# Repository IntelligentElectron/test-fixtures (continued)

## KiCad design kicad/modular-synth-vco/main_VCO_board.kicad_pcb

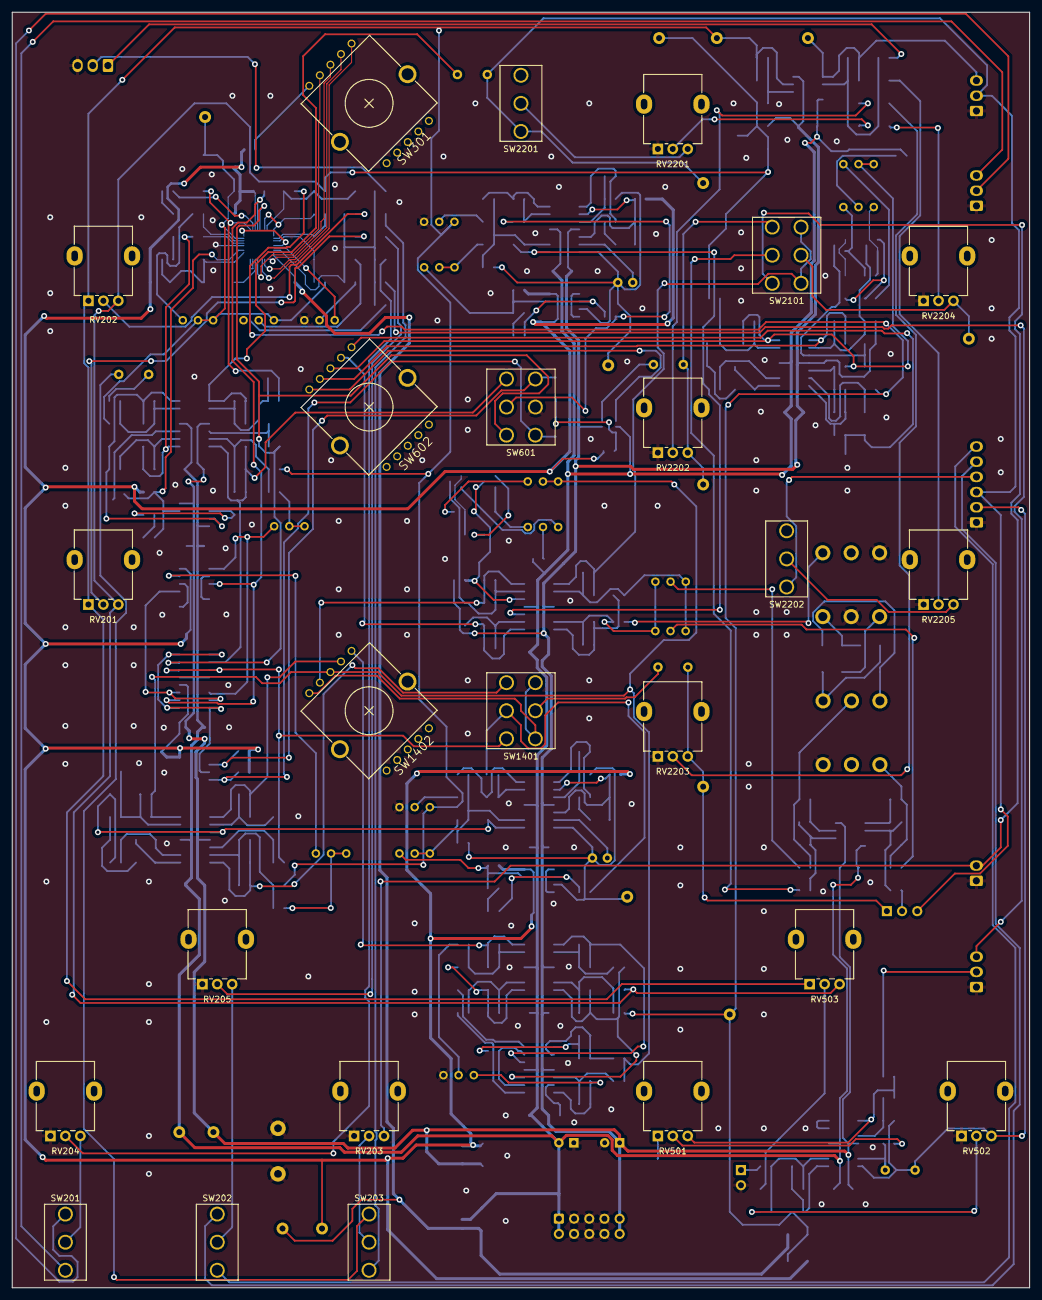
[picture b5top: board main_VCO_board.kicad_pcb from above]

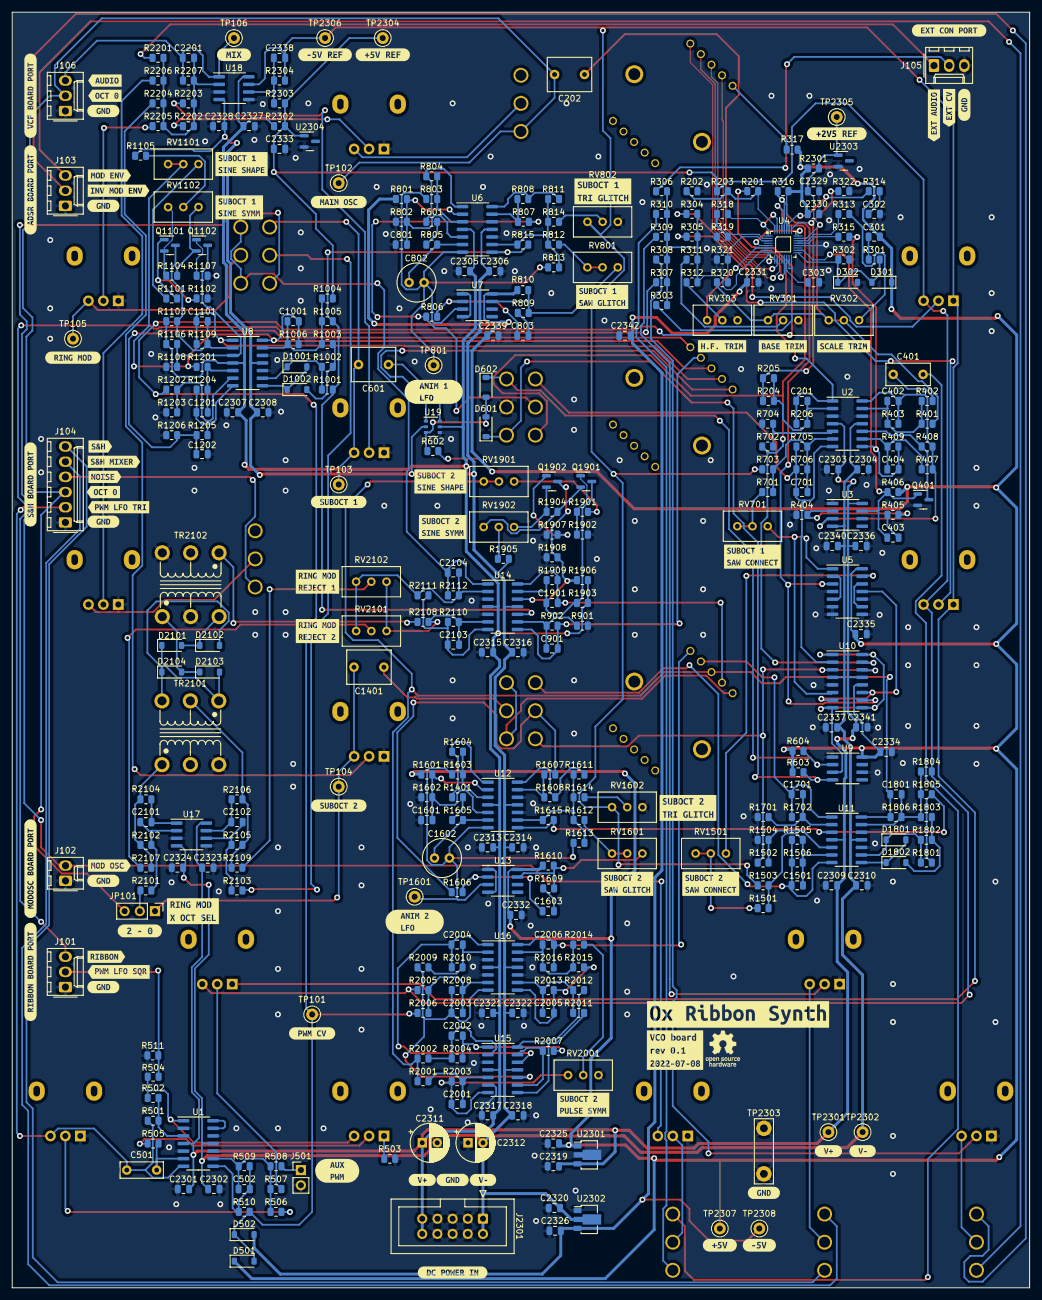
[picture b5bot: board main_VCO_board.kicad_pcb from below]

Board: 2 copper layers, 170.2 x 213.4 mm, 432 parts (408 on the bottom side), 215 nets.

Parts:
C201, C402, C403, C404, C502, C803, C901, C1001, C1603, C1701, C1801, C2003, C2004, C2005, C2006, C2101, C2102, C2103, C2104: 100p; C_0805_2012Metric
C202, C601, C1401: 1u; C_Rect_L7.2mm_W5.5mm_P5.00mm_FKS2_FKP2_MKS2_MKP2
C301, C801, C1601: 10u; C_0805_2012Metric
C302, C1101, C1202, C1901: 10n; C_0805_2012Metric
C303: 3N9 COG; C_0805_2012Metric
C401: 10u BP; C_Rect_L7.2mm_W3.5mm_P5.00mm_FKS2_FKP2_MKS2_MKP2
C501: 220n; C_Rect_L7.0mm_W2.5mm_P5.00mm
C701, C1201, C1501, C2001, C2002, C2201: 10p; C_0805_2012Metric
C802, C1602: 10u BP; C_Radial_D6.3mm_H5.0mm_P2.50mm
C2301, C2302, C2303, C2304, C2305, C2306, C2307, C2308, C2309, C2310, C2313, C2314, C2315, C2316, C2317, C2318, C2321, C2322, C2323, C2324, C2325, C2326, C2327, C2328, C2329, C2330, C2331, C2332, C2333, C2334, C2335, C2336, C2337, C2338, C2339, C2340, C2341, C2342: 100n; C_0805_2012Metric
C2311, C2312: 10u; CP_Radial_D6.3mm_P2.50mm
C2319, C2320: 470n; C_0805_2012Metric
D301, D302, D601, D602, D1001, D1002, D1801, D1802: 1N4148W; D_SOD-123
D501, D502, D2101, D2102, D2103, D2104: BAT48ZFILM; D_SOD-123
J101: ribbon_port; Molex_KK-254_AE-6410-03A_1x03_P2.54mm_Vertical
J102: modosc_port; Molex_KK-254_AE-6410-02A_1x02_P2.54mm_Vertical
J103: ADSR_port; Molex_KK-254_AE-6410-03A_1x03_P2.54mm_Vertical
J104: S&H_port; Molex_KK-254_AE-6410-06A_1x06_P2.54mm_Vertical
J105: ext_con; Molex_KK-254_AE-6410-03A_1x03_P2.54mm_Vertical
J106: vcf_port; Molex_KK-254_AE-6410-03A_1x03_P2.54mm_Vertical
J501: aux_pwm; PinHeader_1x02_P2.54mm_Vertical
J2301: power_entry; IDC-Header_2x05_P2.54mm_Vertical
JP101: rm_x_select; PinHeader_1x03_P2.54mm_Vertical
Q401: 2N7002; SOT-23
Q1101, Q1102, Q1901, Q1902: MMBT3904; SOT-23
R201: 150k; R_0805_2012Metric
R202: 56k; R_0805_2012Metric
R203, R804, R1004, R1006, R1604, R1804, R1806: 120k; R_0805_2012Metric
R204, R205, R304, R306, R307, R308, R309, R310, R311, R317, R401, R403, R405, R501, R505, R506, R507, R508, R509, R602, R704, R705, R706, R805, R807, R808, R809, R811, R813, R815, R902, R1203, R1504, R1505, R1506, R1605, R1607, R1608, R1609, R1611, R1613, R1615, R1702, R2002, R2004, R2008, R2009, R2010, R2011, R2012, R2015, R2101, R2102, R2103, R2105, R2107, R2108, R2109, R2110, R2111, R2201, R2202, R2203, R2204, R2205: 100k; R_0805_2012Metric
R206, R702, R703, R814, R1502, R1503, R1614, R2005, R2006: 200k; R_0805_2012Metric
R301, R302, R406, R603, R604, R803, R1103, R1106, R1201, R1603, R1903, R1906, R2001, R2303, R2304: 10k; R_0805_2012Metric
R303, R402, R901, R1701, R2206: 33k; R_0805_2012Metric
R305: 1M; R_0805_2012Metric
R312, R502: 270k; R_0805_2012Metric
R313: 47k; R_0805_2012Metric
R314: 270; R_0805_2012Metric
R315: 470k; R_0805_2012Metric
R316, R319, R321, R2302: 4k7; R_0805_2012Metric
R318: 3k9; R_0805_2012Metric
R320, R1108, R1109, R1908, R1909: 12k; R_0805_2012Metric
R322, R1105, R1905: 18k; R_0805_2012Metric
R404, R503: 100; R_0805_2012Metric
R407, R408, R409, R2013: 20k; R_0805_2012Metric
R504, R1102, R1107, R1205, R1902, R1907, R2007: 2k2; R_0805_2012Metric
R510, R511, R806, R810, R1206, R1606, R1610: 1k; R_0805_2012Metric
R601: 1M5; R_0805_2012Metric
R701, R812, R1501, R1612, R2016: 180k; R_0805_2012Metric
R801, R1601: 8k2; R_0805_2012Metric
R802, R1602: 2k7; R_0805_2012Metric
R1001, R1002, R1005, R1202, R1801, R1802, R1805: 15k; R_0805_2012Metric
R1003, R1803: 7k5; R_0805_2012Metric
R1101, R1901: 27k; R_0805_2012Metric
R1104, R1904: 390; R_0805_2012Metric
R1204, R2003: 10M; R_0805_2012Metric
R1401: 2M2; R_0805_2012Metric
R2014: 220k; R_0805_2012Metric
R2104, R2106: 330; R_0805_2012Metric
R2112: 560k; R_0805_2012Metric
R2207: 82k; R_0805_2012Metric
R2301: 1k8; R_0805_2012Metric
RV201, RV202: 10k; Potentiometer_Alpha_RD901F-40-00D_Single_Vertical
RV203, RV204, RV205, RV501, RV502, RV503, RV2201, RV2202, RV2203, RV2204, RV2205: 100k; Potentiometer_Alpha_RD901F-40-00D_Single_Vertical
RV301, RV302, RV303, RV802, RV1602: 5k; Potentiometer_Bourns_3296W_Vertical
RV701, RV801, RV1101, RV1102, RV1501, RV1601, RV1901, RV1902, RV2001, RV2101, RV2102: 50k; Potentiometer_Bourns_3296W_Vertical
SW201, SW202, SW203: SW_SPDT_CO; SPDT_mini_toggle
SW301, SW602, SW1402: SR1712F-0204; SR1712F_rotary_switch
SW601, SW1401, SW2101: SW_DPDT_CO; DPDT_mini_toggle
SW2201, SW2202: SW_SPDT; SPDT_mini_toggle
TP101: pwm_cv; TestPoint_Keystone_5000-5004_Miniature
TP102: oct_0; TestPoint_Keystone_5000-5004_Miniature
TP103: oct_1; TestPoint_Keystone_5000-5004_Miniature
TP104: oct_2; TestPoint_Keystone_5000-5004_Miniature
TP105: ring_mod; TestPoint_Keystone_5000-5004_Miniature
TP106: mix; TestPoint_Keystone_5000-5004_Miniature
TP801, TP1601: anim_LFO; TestPoint_Keystone_5000-5004_Miniature
TP2301: V+; TestPoint_Keystone_5000-5004_Miniature
TP2302: V-; TestPoint_Keystone_5000-5004_Miniature
TP2303: GND; TestPoint_Bridge_Pitch7.62mm_Drill1.3mm
TP2304: +5_REF; TestPoint_Keystone_5000-5004_Miniature
TP2305: +2V5; TestPoint_Keystone_5000-5004_Miniature
TP2306: -5_REF; TestPoint_Keystone_5000-5004_Miniature
TP2307: +5; TestPoint_Keystone_5000-5004_Miniature
TP2308: -5; TestPoint_Keystone_5000-5004_Miniature
TR2101, TR2102: Triad_TY_141P; Triad_TY-141P
U1, U2, U6, U8, U11, U12, U14, U15, U16: TL074; SOIC-14_3.9x8.7mm_P1.27mm
U3, U7, U13: LM311; SOIC-8_3.9x4.9mm_P1.27mm
U4: SSI2130; PQN32_HandSoldering
U5: 4013; SOIC-14_3.9x8.7mm_P1.27mm
U9: LM555xM; SOIC-8_3.9x4.9mm_P1.27mm
U10: DG413xY; SOIC-16_3.9x9.9mm_P1.27mm
U17: NE5532; SOIC-8_3.9x4.9mm_P1.27mm
U18: TL072; SOIC-8_3.9x4.9mm_P1.27mm
U19: DG447DV; TSOP-6_1.65x3.05mm_P0.95mm
U2301: L78L05_SOT89; SOT-89-3
U2302: L79L05_SOT89; SOT-89-3
U2303: LM4040C-2.5; SOT-23
U2304: LM4040DBZ-5; SOT-23
kibuzzard-62AC7A9F: G***; kibuzzard-62AC7A9F
kibuzzard-62AF4ADF, kibuzzard-62AF4ADF#2, kibuzzard-62AF4ADF#3, kibuzzard-62AF4ADF#4, kibuzzard-62AF4ADF#5, kibuzzard-62AF4ADF#6, kibuzzard-62AF4ADF#7, kibuzzard-62AF4ADF#8: G***; kibuzzard-62AF4ADF
kibuzzard-62AF4B86: G***; kibuzzard-62AF4B86
kibuzzard-62AF4B95: G***; kibuzzard-62AF4B95
kibuzzard-62AF4BB4: G***; kibuzzard-62AF4BB4
kibuzzard-62AF4BC9: G***; kibuzzard-62AF4BC9
kibuzzard-62AF4BDF: G***; kibuzzard-62AF4BDF
kibuzzard-62AF4C29: G***; kibuzzard-62AF4C29
kibuzzard-62AF4C42: G***; kibuzzard-62AF4C42
kibuzzard-62AF4C77: G***; kibuzzard-62AF4C77
kibuzzard-62AF4C86, kibuzzard-62AF4C86#2: G***; kibuzzard-62AF4C86
kibuzzard-62AF4CA7: G***; kibuzzard-62AF4CA7
kibuzzard-62AF4CDD: G***; kibuzzard-62AF4CDD
kibuzzard-62AF4D2D: G***; kibuzzard-62AF4D2D
kibuzzard-62AF4D5F: G***; kibuzzard-62AF4D5F
kibuzzard-62AF4D40: G***; kibuzzard-62AF4D40
kibuzzard-62AF4D77: G***; kibuzzard-62AF4D77
kibuzzard-62AF4D92: G***; kibuzzard-62AF4D92
kibuzzard-62AF7B29: G***; kibuzzard-62AF7B29
kibuzzard-62AF7B45: G***; kibuzzard-62AF7B45
kibuzzard-62AF7B57: G***; kibuzzard-62AF7B57
kibuzzard-62AF7BF6: G***; kibuzzard-62AF7BF6
kibuzzard-62AF7C0F: G***; kibuzzard-62AF7C0F
kibuzzard-62AF7C6F: G***; kibuzzard-62AF7C6F
kibuzzard-62AF7C97: G***; kibuzzard-62AF7C97
kibuzzard-62AF7CA9: G***; kibuzzard-62AF7CA9
kibuzzard-62AF7CE8: G***; kibuzzard-62AF7CE8
kibuzzard-62AF7D4C: G***; kibuzzard-62AF7D4C
kibuzzard-62AF7D08: G***; kibuzzard-62AF7D08
kibuzzard-62AF7D9E: G***; kibuzzard-62AF7D9E
kibuzzard-62AF7D77: G***; kibuzzard-62AF7D77
kibuzzard-62AF7D91: G***; kibuzzard-62AF7D91
kibuzzard-62AF794D: G***; kibuzzard-62AF794D
kibuzzard-62AF7971, kibuzzard-62AF7971#2: G***; kibuzzard-62AF7971
kibuzzard-62AF7983, kibuzzard-62AF7983#2: G***; kibuzzard-62AF7983
kibuzzard-62B06A0C: G***; kibuzzard-62B06A0C
kibuzzard-62B8B2A5: G***; kibuzzard-62B8B2A5
kibuzzard-62B8B20F: G***; kibuzzard-62B8B20F
kibuzzard-62B8B280: G***; kibuzzard-62B8B280
kibuzzard-62B057A7: G***; kibuzzard-62B057A7
kibuzzard-62B062C4: G***; kibuzzard-62B062C4
kibuzzard-62B0579A: G***; kibuzzard-62B0579A
kibuzzard-62B0634B: G***; kibuzzard-62B0634B
kibuzzard-62B05771: G***; kibuzzard-62B05771
kibuzzard-62B05783: G***; kibuzzard-62B05783
kibuzzard-62B05837: G***; kibuzzard-62B05837
kibuzzard-62C86AB4: G***; kibuzzard-62C86AB4
kibuzzard-62C860A0: G***; kibuzzard-62C860A0
kibuzzard-62C861D2: G***; kibuzzard-62C861D2
kibuzzard-62C861DC: G***; kibuzzard-62C861DC
kibuzzard-62C862AA: G***; kibuzzard-62C862AA
kibuzzard-62C863A9: G***; kibuzzard-62C863A9
kibuzzard-62C863C2: G***; kibuzzard-62C863C2
kibuzzard-62C8621C: G***; kibuzzard-62C8621C
kibuzzard-62C8628B: G***; kibuzzard-62C8628B
kibuzzard-62C86136: G***; kibuzzard-62C86136
kibuzzard-62C86170: G***; kibuzzard-62C86170

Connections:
+2V5_REF: C2329.1, R303.2, R320.2, R401.2, R2301.2, RV301.3, RV302.2, RV302.3, TP2305.1, U4.23 (vref), U2303.1 (K)
+5V: C301.2, C2325.1, C2330.1, C2332.1, C2334.1, C2335.1, C2339.1, D301.1 (K), D501.1 (K), R316.2, R317.1, R406.2, R602.2, R603.1, R604.1, R801.1, R810.2, R1601.1, R1610.2, R2301.1, TP2307.1, U4.27 (V+), U5.14 (VDD), U7.8 (V+), U9.8 (VCC), U10.12 (VL), U13.8 (V+), U2301.1 (OUT)
+5V_REF: C2333.1, R203.1, R1004.2, R1804.2, R2005.1, R2302.2, R2303.2, RV201.3, RV202.3, RV503.3, TP2304.1, U2304.1 (K)
+15V: C2301.1, C2303.1, C2305.1, C2307.1, C2309.1, C2311.1, C2313.1, C2315.1, C2317.1, C2319.1, C2321.1, C2323.1, C2327.1, C2336.1, C2341.1, J2301.9, J2301.10, R1103.1, R1106.1, R1903.1, R1906.1, R2302.1, TP2301.1, U1.4 (V+), U2.4 (V+), U3.8 (V+), U6.4 (V+), U8.4 (V+), U10.13 (V+), U11.4 (V+), U12.4 (V+), U14.4 (V+), U15.4 (V+), U16.4 (V+), U17.8 (V+), U18.8 (V+), U19.5 (V+), U2301.3 (IN)
-5V: C2326.2, C2331.2, C2342.2, D502.2 (A), TP2308.1, U4.8 (V-), U2302.3 (VO)
-5V_REF: C2338.1, R703.1, R1503.1, R2304.1, RV201.1, RV202.1, RV503.1, RV802.3, RV1602.3, TP2306.1, U18.7
-15V: C2302.2, C2304.2, C2306.2, C2308.2, C2310.2, C2312.2, C2314.2, C2316.2, C2318.2, C2320.2, C2322.2, C2324.2, C2328.2, C2337.2, C2340.2, J2301.1, J2301.2, R1105.2, R1905.2, TP2302.1, U1.11 (V-), U2.11 (V-), U3.4 (V-), U6.11 (V-), U8.11 (V-), U10.4 (V-), U11.11 (V-), U12.11 (V-), U14.11 (V-), U15.11 (V-), U16.11 (V-), U17.4 (V-), U18.4 (V-), U19.2 (V-), U2302.2 (VI)
/EXT_AUDIO: J105.1, R2201.1
/MOD_OSC: J102.2, RV203.3, SW2101.1
/NOISE: J104.4, SW2202.1 (A)
/OCTAVE_0: C202.2, J104.3, J106.2, JP101.3 (B), SW2201.1 (A), TP102.1
/OCTAVE_1: C601.2, RV2202.3, SW2101.3, TP103.1
/OCTAVE_2: C1401.2, JP101.1 (A), RV2203.3, TP104.1
/PWM_LFO_SQR: J101.2, R504.1, R511.2
/PWM_LFO_TRI: C501.2, J104.2, R501.2, RV502.3, U1.7
/PWM_generator/PWM_CV_OUT: D501.2 (A), D502.1 (K), R201.1, R510.2, R1202.1, R2006.1, TP101.1
/audio_mixer/OUT: C2201.2, J106.3, R2207.2, TP106.1, U18.1
/audio_mixer/RING_MOD: RV2204.3, SW2101.5, TP105.1
/main_VCO/EXT_CV: J105.2, R306.2
/main_VCO/MOD_ENV_DOWN: J103.2, SW201.3
/main_VCO/MOD_ENV_UP: J103.3, SW201.1
/main_VCO/RIBBON_CV: J101.3, R307.2
/main_VCO/S_AND_H: J104.6, SW202.1
/main_VCO/S_AND_H_MIXER: J104.5, SW202.3
/main_VCO/VCO_core/COARSE_TUNE_IN: R304.2, RV202.2
/main_VCO/VCO_core/FINE_TUNE_IN: R305.2, RV201.2
/main_VCO/VCO_core/LIN_FM_IN: C404.1, R315.2, R409.1, U2.8
/main_VCO/VCO_core/PWM_CV_IN: R201.2, R202.1, R203.2, U4.32 (pwm_in_+)
/main_VCO/VCO_core/SWITCHED_OUT: R204.1, R205.1, R322.2, U4.25 (mix_out)
/main_VCO/VCO_core/TIME_REV_IN: C403.1, Q401.1 (G), R406.1, U3.7, U4.18 (time_rev)
/main_VCO/VCO_core/V_PER_OCT_IN_3: R308.2, RV204.2
/main_VCO/VCO_core/V_PER_OCT_IN_4: R309.2, RV205.2
/main_VCO/VCO_core/V_PER_OCT_IN_5: R310.2, SW203.1
/main_VCO/lin_FM_conditioner/LIN_FM_IN: C401.2, SW203.3
/ring_modulator/X_IN: JP101.2 (C), R2101.1
/sub_osc_1/OCT_DWN_SAW: C701.2, R705.2, R706.2, SW601.3, U2.7, U10.2
/sub_osc_1/OCT_DWN_SQR: RV701.1, U5.1 (Q), U10.6
/sub_osc_1/SAW_IN: R702.1, SW601.1, U4.29 (saw_out), U10.15
/sub_osc_1/SINE: C1101.2, R1109.2, SW602.2, U8.1
/sub_osc_1/SQUARE_IN: R316.1, U4.28 (square_out), U5.3 (C), U10.10
/sub_osc_1/SQUARE_OUT: U5.11 (C), U10.7, U10.11
/sub_osc_1/STATIC_SAW_OUT: R1502.1, SW1401.1, U10.3, U10.14
/sub_osc_1/basic_pulse_shaper/PULSE_OUT: C1202.2, R1205.2, R1206.2, SW602.5
/sub_osc_1/basic_pulse_shaper/SIGNAL_IN: C1001.2, R1006.1, R1201.1, RV1101.2, RV1101.3, SW602.3, U8.14
/sub_osc_1/level_shifter_1/IN: R815.2, R1001.2, R1005.2, U6.8, U14.10 (+)
/sub_osc_1/level_shifter_1/OUT: C901.2, R902.2, SW602.4, U14.8
/sub_osc_1/passthrough_switching/SWITCH_0: D602.1 (K), R604.2, SW601.6, U9.2 (TR)
/sub_osc_1/passthrough_switching/SWITCH_1: D601.1 (K), R603.2, SW601.4, U9.4 (R)
/sub_osc_1/passthrough_switching/SWITCH_CTL: U9.3 (Q), U10.1, U10.8, U10.9, U10.16
/sub_osc_1/saw_animator_1/RATE_R_1: R601.1, R804.2, U6.1
/sub_osc_1/saw_animator_1/RATE_R_2: R601.2, R805.1
/sub_osc_1/saw_animator_1/SAW_IN: R806.1, R807.1, SW601.2
/sub_osc_1/~OUTPUT_ENABLE: D601.2 (A), D602.2 (A), R602.1, U19.3
/sub_osc_2/SINE: C1901.2, R1909.2, SW1402.2, U14.14
/sub_osc_2/harmonic_pulse_shaper/PULSE_OUT: C2006.2, R2016.2, SW1402.5, U16.14
/sub_osc_2/harmonic_pulse_shaper/SIGNAL_IN: C1801.2, R1806.1, R2001.1, R2002.1, RV1901.2, RV1901.3, SW1402.3, U11.14
/sub_osc_2/level_shifter_2/IN: R1615.2, R1801.2, R1805.2, U11.3 (+), U12.8
/sub_osc_2/level_shifter_2/OUT: C1701.2, R1702.2, SW1402.4, U11.1
/sub_osc_2/octave_divider_2/OCTAVE_DOWN_SAW_OUT: C1501.2, R1505.2, R1506.2, SW1401.3, U11.7
/sub_osc_2/octave_divider_2/OCTAVE_DOWN_SQR_OUT: RV1501.1, U5.13 (Q)
/sub_osc_2/saw_animator_2/RATE_R_1: R1401.1, R1604.2, U12.1
/sub_osc_2/saw_animator_2/RATE_R_2: R1401.2, R1605.1
/sub_osc_2/saw_animator_2/SAW_IN: R1606.1, R1607.1, SW1401.2
GND: C302.2, C303.2, C801.2, C1202.1, C1601.2, C2301.2, C2302.1, C2303.2, C2304.1, C2305.2, C2306.1, C2307.2, C2308.1, C2309.2, C2310.1, C2311.2, C2312.1, C2313.2, C2314.1, C2315.2, C2316.1, C2317.2, C2318.1, C2319.2, C2320.1, C2321.2, C2322.1, C2323.2, C2324.1, C2325.2, C2326.1, C2327.2, C2328.1, C2329.2, C2330.2, C2331.1, C2332.2, C2333.2, C2334.2, C2335.2, C2336.2, C2337.1, C2339.2, C2340.1, C2341.2, C2342.1, D302.2 (A), J101.1, J102.1, J103.1, J104.1, J105.3, J106.1, J501.2, J2301.3, J2301.4, J2301.5, J2301.6, J2301.7, J2301.8, Q401.2 (S), R202.2, R302.2, R319.1, R321.1, R322.1, R404.1, R503.2, R511.1, R704.2, R802.2, R901.1, R1102.2, R1107.2, R1108.1, R1203.2, R1206.1, R1504.2, R1602.2, R1701.1, R1902.2, R1907.2, R1908.1, RV203.1, RV204.1, RV205.1, RV301.1, RV303.1, RV502.1, RV802.1, RV1602.1, RV2001.1, RV2201.1, RV2202.1, RV2203.1, RV2204.1, RV2205.1, SW601.5, TP2303.1, TR2101.3, TR2102.2, TR2102.6, U1.2 (-), U1.5 (+), U1.10 (+), U1.12 (+), U2.3 (+), U2.12 (+), U3.1 (GND), U4.15 (dgnd), U4.16 (agnd), U4.20 (hft_base), U5.4 (R), U5.6 (S), U5.7 (VSS), U5.8 (S), U5.10 (R), U6.10 (+), U6.12 (+), U7.1 (GND), U7.4 (V-), U8.10 (+), U8.12 (+), U9.1 (GND), U9.6 (THR), U10.5 (GND), U11.10 (+), U11.12 (+), U12.10 (+), U12.12 (+), U13.1 (GND), U13.4 (V-), U14.3 (+), U14.5 (+), U15.3 (+), U15.6 (-), U16.3 (+), U16.5 (+), U16.10 (+), U16.12 (+), U17.3 (+), U17.5 (+), U18.3 (+), U18.5 (+), U19.4 (GND), U2301.2 (GND), U2302.1 (GND), U2303.2 (A), U2304.2 (A)
unnamed: C201.2, C202.1, R206.2, U2.1
unnamed: C301.1, R301.1
unnamed: C302.1, R314.2
unnamed: C401.1, R402.2
unnamed: C403.2, R405.1
unnamed: C502.2, R509.2, R510.1, U1.8
unnamed: C601.1, U19.6
unnamed: C803.2, R809.1
unnamed: C1201.2, R1204.2, R1205.1, U8.7
unnamed: C1401.1, SW1401.5
unnamed: C1603.2, R1609.1
unnamed: C2001.2, R2003.2, RV2001.3, U15.7
unnamed: C2002.2, R2004.2, R2007.1, U15.1
unnamed: C2005.2, R2013.2, R2015.1, U16.8
unnamed: C2101.2, R2104.1, U17.1
unnamed: C2102.2, R2106.1, U17.7
unnamed: C2103.2, R2110.2, R2111.1, U14.7
unnamed: C2104.2, R2112.2, SW2101.4, SW2101.6, U14.1
unnamed: D301.2 (A), D302.1 (K), R301.2, R302.1, U4.17 (hard_sync)
unnamed: D1001.2 (A), D1002.1 (K), U8.8
unnamed: D1001.1 (K), R1001.1, R1002.2, U8.9 (-)
unnamed: D1002.2 (A), R1002.1, R1003.2
unnamed: D1801.2 (A), D1802.1 (K), U11.8
unnamed: D1801.1 (K), R1801.1, R1802.2, U11.9 (-)
unnamed: D1802.2 (A), R1802.1, R1803.2
unnamed: D2101.2 (A), D2102.1 (K), TR2102.3
unnamed: D2101.1 (K), D2103.2 (A), TR2101.4
unnamed: D2102.2 (A), D2104.1 (K), TR2101.6
unnamed: D2103.1 (K), D2104.2 (A), TR2102.1
unnamed: J501.1, R508.1
unnamed: Q401.3 (D), R408.1, U2.10 (+)
unnamed: Q1101.1 (B), R1101.2, R1102.1
unnamed: C1101.1, Q1101.3 (C), R1103.2, R1109.1, U8.2 (-)
unnamed: Q1101.2 (E), R1104.1, RV1102.3
unnamed: Q1102.1 (B), R1107.1
unnamed: Q1102.3 (C), R1106.2, R1108.2, U8.3 (+)
unnamed: Q1102.2 (E), R1104.2, RV1102.1
unnamed: Q1901.1 (B), R1901.2, R1902.1
unnamed: C1901.1, Q1901.3 (C), R1903.2, R1909.1, U14.13 (-)
unnamed: Q1901.2 (E), R1904.1, RV1902.3
unnamed: Q1902.1 (B), R1907.1
unnamed: Q1902.3 (C), R1906.2, R1908.2, U14.12 (+)
unnamed: Q1902.2 (E), R1904.2, RV1902.1
unnamed: R311.2, RV301.2
unnamed: R312.1, RV303.2
unnamed: R313.1, RV302.1
unnamed: R317.2, SW301.1
unnamed: R502.2, R504.2, RV501.3, U1.1
unnamed: R503.1, RV501.1
unnamed: R505.1, RV501.2
unnamed: R506.1, RV502.2
unnamed: R507.1, RV503.2
unnamed: R701.1, RV701.2, RV701.3
unnamed: R808.2, R811.1, U6.14
unnamed: R809.2, R810.1, RV801.1, U7.7
unnamed: R812.1, RV801.2, RV801.3
unnamed: R814.1, RV802.2
unnamed: R1101.1, RV1101.1
unnamed: R1105.1, RV1102.2
unnamed: R1501.1, RV1501.2, RV1501.3
unnamed: R1608.2, R1611.1, U12.14
unnamed: R1609.2, R1610.1, RV1601.1, U13.7
unnamed: R1612.1, RV1601.2, RV1601.3
unnamed: R1614.1, RV1602.2
unnamed: R1901.1, RV1901.1
unnamed: R1905.1, RV1902.2
unnamed: R2011.1, U15.8
unnamed: R2012.1, U15.14
unnamed: R2014.1, RV2001.2
unnamed: R2102.2, R2104.2, R2107.1, TR2101.1
unnamed: R2103.1, SW2101.2
unnamed: R2105.2, R2106.2, R2109.1, TR2101.5
unnamed: R2107.2, RV2101.2
unnamed: R2108.1, TR2102.4
unnamed: R2109.2, RV2102.2
unnamed: R2202.1, RV2201.2
unnamed: R2203.1, RV2202.2
unnamed: R2204.1, RV2203.2
unnamed: R2205.1, RV2204.2
unnamed: R2206.1, RV2205.2
unnamed: RV203.2, SW203.2
unnamed: RV204.3, SW201.2
unnamed: RV205.3, SW202.2
unnamed: SW602.1, U19.1
unnamed: SW1401.4, SW1401.6, SW1402.1
unnamed: RV2201.3, SW2201.2 (B)
unnamed: RV2205.3, SW2202.2 (B)
unnamed: R501.1, R502.1, U1.3 (+)
unnamed: C501.1, R505.2, U1.6 (-)
unnamed: C502.1, R506.2, R507.2, R508.2, R509.1, U1.9 (-)
unnamed: U1.13 (-), U1.14
unnamed: C201.1, R204.2, R205.2, R206.1, U2.2 (-)
unnamed: R702.2, R704.1, U2.5 (+)
unnamed: C701.1, R701.2, R703.2, R705.1, R706.1, U2.6 (-)
unnamed: C404.2, R407.1, R409.2, U2.9 (-)
unnamed: C402.2, R401.1, R402.1, R403.2, U2.13 (-)
unnamed: R404.2, R405.2, U3.2 (+)
unnamed: C402.1, R403.1, R407.2, R408.2, U2.14, U3.3 (-)
unnamed: RV303.3, U4.6 (hf_track)
unnamed: R315.1, U4.21 (lin_freq)
unnamed: C303.1, U4.14 (tcap)
unnamed: R318.2, U4.1 (tri_out), U4.31 (pwm_in_-)
unnamed: R314.1, U4.26 (bw_comp)
unnamed: R303.1, R304.1, R305.1, R306.1, R307.1, R308.1, R309.1, R310.1, R311.1, R312.2, U4.7 (expo_freq)
unnamed: R313.2, U4.22 (expo_scale)
unnamed: R318.1, R319.2, U4.2 (sine_in_+)
unnamed: R320.1, R321.2, U4.3 (sine_in_-)
unnamed: U4.5 (aux_in_2), U4.24 (sine_out)
unnamed: SW301.2, U4.13 (aux_2_mix)
unnamed: SW301.5, U4.11 (pulse_mix)
unnamed: SW301.4, U4.10 (saw_mix)
unnamed: SW301.3, U4.9 (tri_mix)
unnamed: U5.2 (~Q), U5.5 (D)
unnamed: U5.9 (D), U5.12 (~Q)
unnamed: R803.1, R804.1, U6.3 (+)
unnamed: C801.1, R801.2, R802.1, U6.2 (-), U6.5 (+)
unnamed: C802.1, R805.2, U6.6 (-)
unnamed: R811.2, R812.2, R813.1, R814.2, R815.1, U6.9 (-)
unnamed: R807.2, R808.1, U6.13 (-)
unnamed: C803.1, R806.2, U7.2 (+)
unnamed: C802.2, R803.2, R813.2, TP801.1, U6.7, U7.3 (-)
unnamed: C1201.1, R1201.2, R1204.1, U8.5 (+)
unnamed: R1202.2, R1203.1, U8.6 (-)
unnamed: C1001.1, R1003.1, R1004.1, R1005.1, R1006.2, U8.13 (-)
unnamed: C1701.1, R1701.2, R1702.1, U11.2 (-)
unnamed: R1502.2, R1504.1, U11.5 (+)
unnamed: C1501.1, R1501.2, R1503.2, R1505.1, R1506.1, U11.6 (-)
unnamed: C1801.1, R1803.1, R1804.1, R1805.1, R1806.2, U11.13 (-)
unnamed: R1603.1, R1604.1, U12.3 (+)
unnamed: C1601.1, R1601.2, R1602.1, U12.2 (-), U12.5 (+)
unnamed: C1602.1, R1605.2, U12.6 (-)
unnamed: R1611.2, R1612.2, R1613.1, R1614.2, R1615.1, U12.9 (-)
unnamed: R1607.2, R1608.1, U12.13 (-)
unnamed: C1603.1, R1606.2, U13.2 (+)
unnamed: C1602.2, R1603.2, R1613.2, TP1601.1, U12.7, U13.3 (-)
unnamed: C2104.1, R2111.2, R2112.1, RV2101.3, RV2102.3, U14.2 (-)
unnamed: C2103.1, R2108.2, R2110.1, RV2101.1, RV2102.1, U14.6 (-)
unnamed: C901.1, R901.2, R902.1, U14.9 (-)
unnamed: C2002.1, R2002.2, R2004.1, U15.2 (-)
unnamed: C2001.1, R2001.2, R2003.1, U15.5 (+)
unnamed: C2003.2, R2008.2, R2009.1, U15.10 (+), U16.7
unnamed: R2007.2, U15.9 (-), U15.13 (-)
unnamed: C2004.2, R2010.2, U15.12 (+), U16.1
unnamed: C2004.1, R2009.2, R2010.1, U16.2 (-)
unnamed: C2003.1, R2005.2, R2006.2, R2008.1, U16.6 (-)
unnamed: C2005.1, R2011.2, R2012.2, R2013.1, U16.9 (-)
unnamed: C2006.1, R2014.2, R2015.2, R2016.1, U16.13 (-)
unnamed: C2101.1, R2101.2, R2102.1, U17.2 (-)
unnamed: C2102.1, R2103.2, R2105.1, U17.6 (-)
unnamed: C2201.1, R2201.2, R2202.2, R2203.2, R2204.2, R2205.2, R2206.2, R2207.1, U18.2 (-)
unnamed: C2338.2, R2303.1, R2304.2, U18.6 (-)

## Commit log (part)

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2026-03-19 Add EDA test fixtures (Altium, Cadence)
    Consolidate test fixture data from individual forks into a single
    monorepo. LimeSDR-USB includes only hardware/ to reduce size.
2026-03-19 Remove .mcp.json from BeagleBone-Black fixture
2026-03-23 Add BeagleBone Black fixture from beagleboard.org fork
    Forked from beagleboard/beaglebone-black to IntelligentElectron/beaglebone-black (private).
    This is the actively maintained Rev C3 design, separate from the existing CircuitCo-sourced fixture.
2026-03-23 Add .gitignore to exclude .claude/ directory
2026-03-25 Add 10 KiCad test fixtures ranging from simple to complex
    Simple (2-layer, <10 components):
    - 555-blinker-pcb: LED blinker with NE555P timer
    - Getting-to-Blinky: CMOS 555 LED blinker
    - kicad_usbc_breakout: USB-C breakout board
    Medium (2-4 layers, 30-120 components):
    - ESP32-C3-DevBoard: ESP32-C3 RISC-V dev board
2026-03-25 Add KiCad fixtures attribution to NOTICE.md
